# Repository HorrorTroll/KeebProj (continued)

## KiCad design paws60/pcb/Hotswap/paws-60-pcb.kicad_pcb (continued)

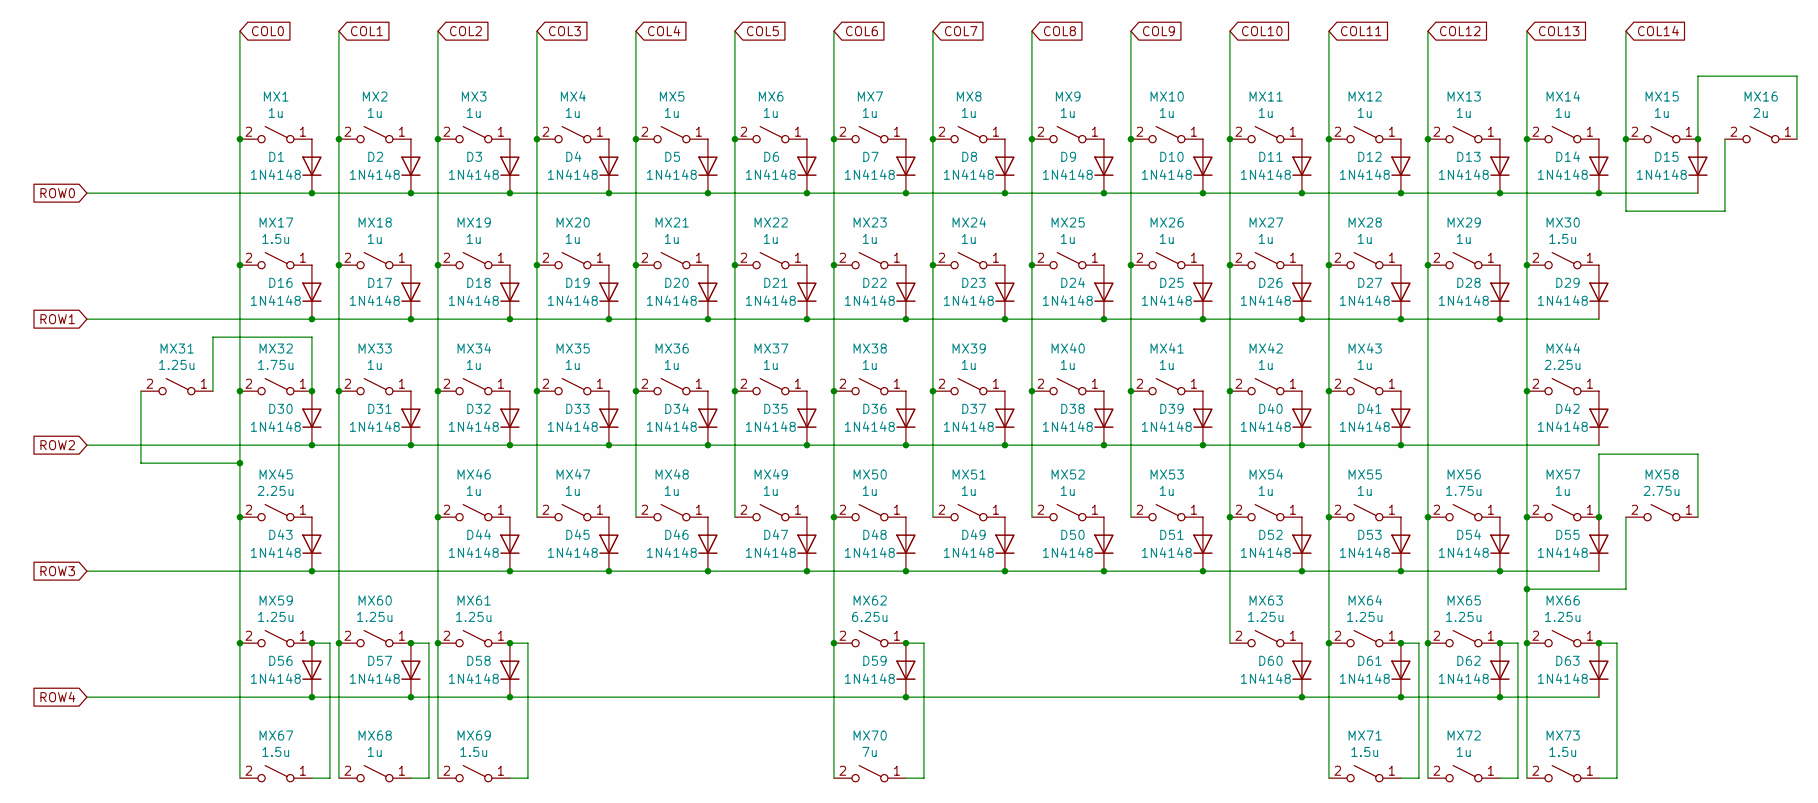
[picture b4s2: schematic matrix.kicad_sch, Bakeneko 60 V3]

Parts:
D1, D2, D3, D4, D5, D6, D7, D8, D9, D10, D11, D12, D13, D14, D15, D16, D17, D18, D19, D20, D21, D22, D23, D24, D25, D26, D27, D28, D29, D30, D31, D32, D33, D34, D35, D36, D37, D38, D39, D40, D41, D42, D43, D44, D45, D46, D47, D48, D49, D50, D51, D52, D53, D54, D55, D56, D57, D58, D59, D60, D61, D62, D63: 1N4148; D_SOD-123; LCSC Part # C81598
MX1, MX2, MX3, MX4, MX5, MX6, MX7, MX8, MX9, MX10, MX11, MX12, MX13, MX14, MX15, MX18, MX19, MX20, MX21, MX22, MX23, MX24, MX25, MX26, MX27, MX28, MX29, MX33, MX34, MX35, MX36, MX37, MX38, MX39, MX40, MX41, MX42, MX43, MX46, MX47, MX48, MX49, MX50, MX51, MX52, MX53, MX54, MX55, MX57, MX68, MX72: 1u; MXOnly-1U-Hotswap
MX16: 2u; MXOnly-2U-Hotswap
MX17, MX30, MX67, MX69, MX71, MX73: 1.5u; MXOnly-1.5U-Hotswap
MX31, MX59, MX60, MX61, MX63, MX64, MX65, MX66: 1.25u; MXOnly-1.25U-Hotswap
MX32, MX56: 1.75u; MXOnly-1.75U-Hotswap
MX44, MX45: 2.25u; MXOnly-2.25U-Hotswap
MX58: 2.75u; MXOnly-2.75U-Hotswap
MX62: 6.25u; MXOnly-6.25U-Hotswap-ReversedStabilizers
MX70: 7u; MXOnly-7U-Hotswap

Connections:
COL0: MX1.2 (B), MX17.2 (B), MX31.2 (B), MX32.2 (B), MX45.2 (B), MX59.2 (B), MX67.2 (B); also elsewhere on the board
COL1: MX2.2 (B), MX18.2 (B), MX33.2 (B), MX60.2 (B), MX68.2 (B); also elsewhere on the board
COL2: MX3.2 (B), MX19.2 (B), MX34.2 (B), MX46.2 (B), MX61.2 (B), MX69.2 (B); also elsewhere on the board
COL3: MX4.2 (B), MX20.2 (B), MX35.2 (B), MX47.2 (B); also elsewhere on the board
COL4: MX5.2 (B), MX21.2 (B), MX36.2 (B), MX48.2 (B); also elsewhere on the board
COL5: MX6.2 (B), MX22.2 (B), MX37.2 (B), MX49.2 (B); also elsewhere on the board
COL6: MX7.2 (B), MX23.2 (B), MX38.2 (B), MX50.2 (B), MX62.2 (B), MX70.2 (B); also elsewhere on the board
COL7: MX8.2 (B), MX24.2 (B), MX39.2 (B), MX51.2 (B); also elsewhere on the board
COL8: MX9.2 (B), MX25.2 (B), MX40.2 (B), MX52.2 (B); also elsewhere on the board
COL9: MX10.2 (B), MX26.2 (B), MX41.2 (B), MX53.2 (B); also elsewhere on the board
COL10: MX11.2 (B), MX27.2 (B), MX42.2 (B), MX54.2 (B), MX63.2 (B); also elsewhere on the board
COL11: MX12.2 (B), MX28.2 (B), MX43.2 (B), MX55.2 (B), MX64.2 (B), MX71.2 (B); also elsewhere on the board
COL12: MX13.2 (B), MX29.2 (B), MX56.2 (B), MX65.2 (B), MX72.2 (B); also elsewhere on the board
COL13: MX14.2 (B), MX30.2 (B), MX44.2 (B), MX57.2 (B), MX58.2 (B), MX66.2 (B), MX73.2 (B); also elsewhere on the board
COL14: MX15.2 (B), MX16.2 (B); also elsewhere on the board
unnamed: D1.2 (A), MX1.1 (A)
unnamed: D2.2 (A), MX2.1 (A)
unnamed: D3.2 (A), MX3.1 (A)
unnamed: D4.2 (A), MX4.1 (A)
unnamed: D5.2 (A), MX5.1 (A)
unnamed: D6.2 (A), MX6.1 (A)
unnamed: D7.2 (A), MX7.1 (A)
unnamed: D8.2 (A), MX8.1 (A)
unnamed: D9.2 (A), MX9.1 (A)
unnamed: D10.2 (A), MX10.1 (A)
unnamed: D11.2 (A), MX11.1 (A)
unnamed: D12.2 (A), MX12.1 (A)
unnamed: D13.2 (A), MX13.1 (A)
unnamed: D14.2 (A), MX14.1 (A)
unnamed: D15.2 (A), MX15.1 (A), MX16.1 (A)
unnamed: D16.2 (A), MX17.1 (A)
unnamed: D17.2 (A), MX18.1 (A)
unnamed: D18.2 (A), MX19.1 (A)
unnamed: D19.2 (A), MX20.1 (A)
unnamed: D20.2 (A), MX21.1 (A)
unnamed: D21.2 (A), MX22.1 (A)
unnamed: D22.2 (A), MX23.1 (A)
unnamed: D23.2 (A), MX24.1 (A)
unnamed: D24.2 (A), MX25.1 (A)
unnamed: D25.2 (A), MX26.1 (A)
unnamed: D26.2 (A), MX27.1 (A)
unnamed: D27.2 (A), MX28.1 (A)
unnamed: D28.2 (A), MX29.1 (A)
unnamed: D29.2 (A), MX30.1 (A)
unnamed: D30.2 (A), MX31.1 (A), MX32.1 (A)
unnamed: D31.2 (A), MX33.1 (A)
unnamed: D32.2 (A), MX34.1 (A)
unnamed: D33.2 (A), MX35.1 (A)
unnamed: D34.2 (A), MX36.1 (A)
unnamed: D35.2 (A), MX37.1 (A)
unnamed: D36.2 (A), MX38.1 (A)
unnamed: D37.2 (A), MX39.1 (A)
unnamed: D38.2 (A), MX40.1 (A)
unnamed: D39.2 (A), MX41.1 (A)
unnamed: D40.2 (A), MX42.1 (A)
unnamed: D41.2 (A), MX43.1 (A)
unnamed: D42.2 (A), MX44.1 (A)
unnamed: D43.2 (A), MX45.1 (A)
unnamed: D44.2 (A), MX46.1 (A)
unnamed: D45.2 (A), MX47.1 (A)
unnamed: D46.2 (A), MX48.1 (A)
unnamed: D47.2 (A), MX49.1 (A)
unnamed: D48.2 (A), MX50.1 (A)
unnamed: D49.2 (A), MX51.1 (A)
unnamed: D50.2 (A), MX52.1 (A)
unnamed: D51.2 (A), MX53.1 (A)
unnamed: D52.2 (A), MX54.1 (A)
unnamed: D53.2 (A), MX55.1 (A)
unnamed: D54.2 (A), MX56.1 (A)
unnamed: D55.2 (A), MX57.1 (A), MX58.1 (A)
unnamed: D56.2 (A), MX59.1 (A), MX67.1 (A)
unnamed: D57.2 (A), MX60.1 (A), MX68.1 (A)
unnamed: D58.2 (A), MX61.1 (A), MX69.1 (A)
unnamed: D59.2 (A), MX62.1 (A), MX70.1 (A)
unnamed: D60.2 (A), MX63.1 (A)
unnamed: D61.2 (A), MX64.1 (A), MX71.1 (A)
unnamed: D62.2 (A), MX65.1 (A), MX72.1 (A)
unnamed: D63.2 (A), MX66.1 (A), MX73.1 (A)
ROW0: D1.1 (K), D2.1 (K), D3.1 (K), D4.1 (K), D5.1 (K), D6.1 (K), D7.1 (K), D8.1 (K), D9.1 (K), D10.1 (K), D11.1 (K), D12.1 (K), D13.1 (K), D14.1 (K), D15.1 (K); also elsewhere on the board
ROW1: D16.1 (K), D17.1 (K), D18.1 (K), D19.1 (K), D20.1 (K), D21.1 (K), D22.1 (K), D23.1 (K), D24.1 (K), D25.1 (K), D26.1 (K), D27.1 (K), D28.1 (K), D29.1 (K); also elsewhere on the board
ROW2: D30.1 (K), D31.1 (K), D32.1 (K), D33.1 (K), D34.1 (K), D35.1 (K), D36.1 (K), D37.1 (K), D38.1 (K), D39.1 (K), D40.1 (K), D41.1 (K), D42.1 (K); also elsewhere on the board
ROW3: D43.1 (K), D44.1 (K), D45.1 (K), D46.1 (K), D47.1 (K), D48.1 (K), D49.1 (K), D50.1 (K), D51.1 (K), D52.1 (K), D53.1 (K), D54.1 (K), D55.1 (K); also elsewhere on the board
ROW4: D56.1 (K), D57.1 (K), D58.1 (K), D59.1 (K), D60.1 (K), D61.1 (K), D62.1 (K), D63.1 (K); also elsewhere on the board

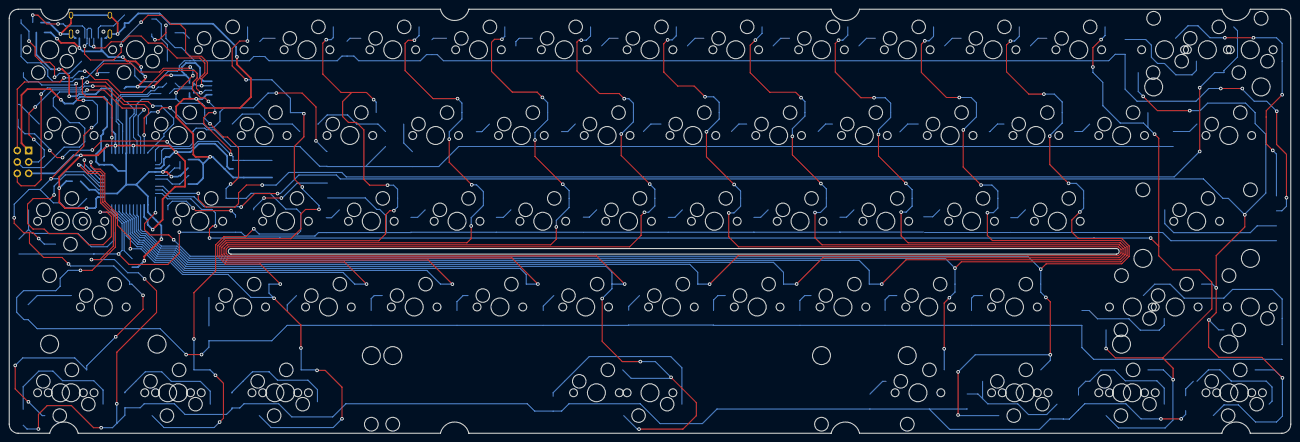
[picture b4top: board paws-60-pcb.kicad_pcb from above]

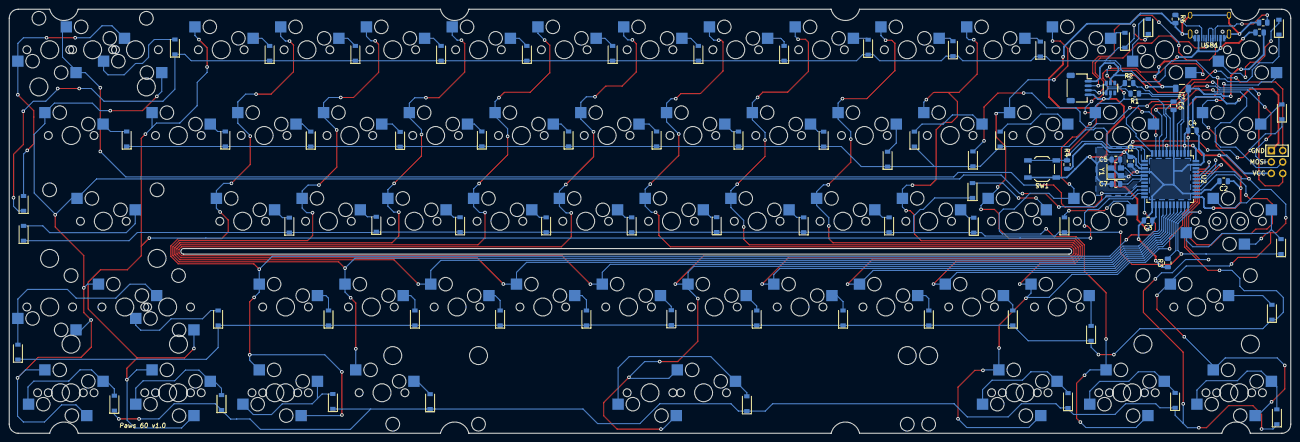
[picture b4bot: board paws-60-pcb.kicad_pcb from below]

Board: 2 copper layers, 284.7 x 94.2 mm, 160 parts (85 on the bottom side), 100 nets.

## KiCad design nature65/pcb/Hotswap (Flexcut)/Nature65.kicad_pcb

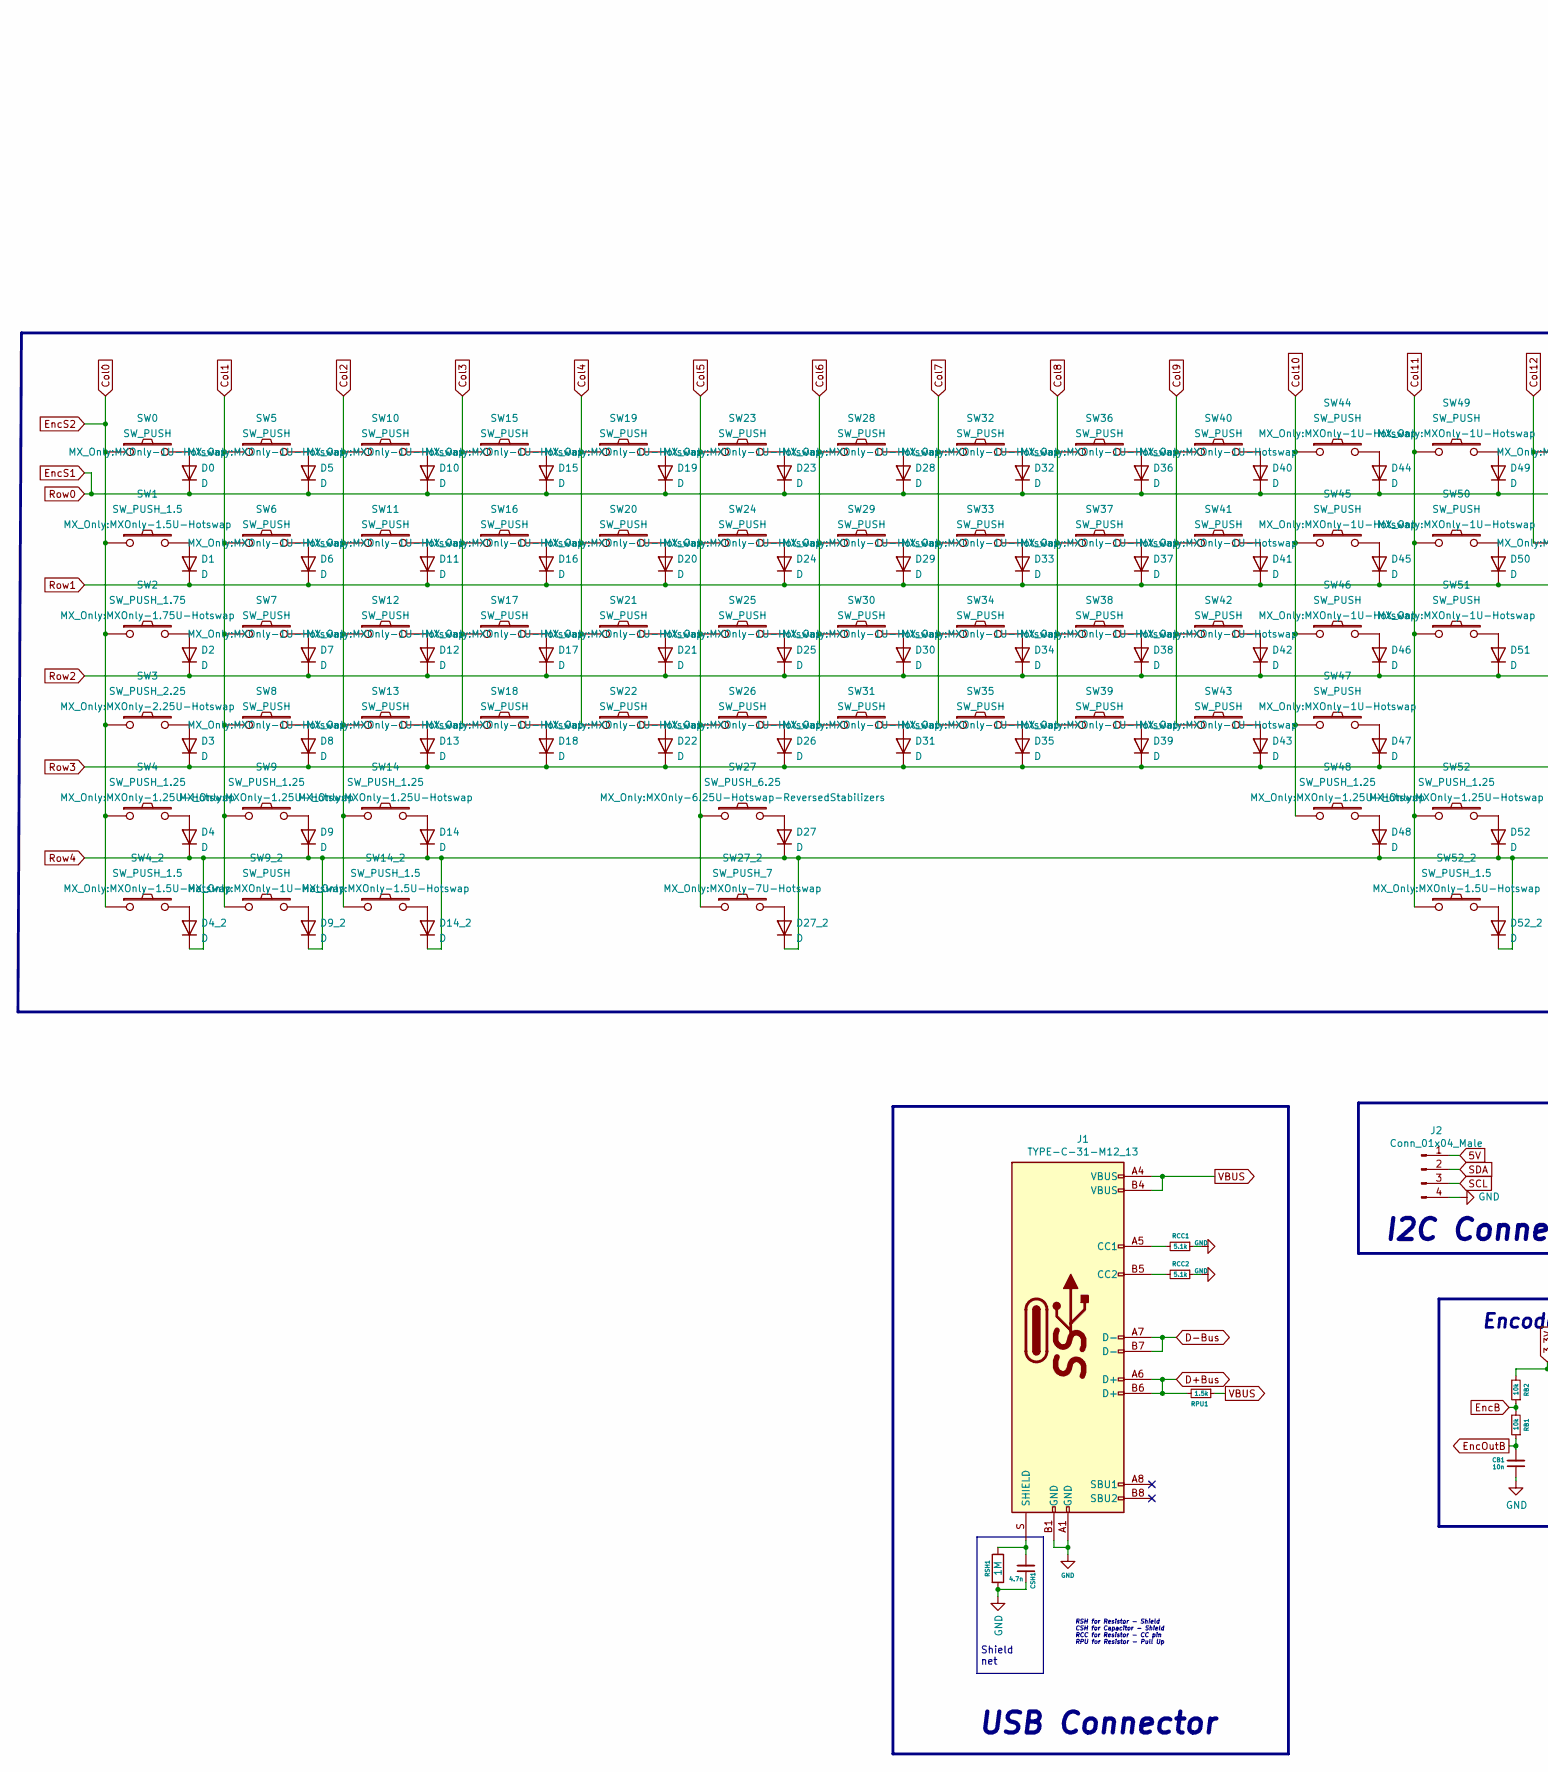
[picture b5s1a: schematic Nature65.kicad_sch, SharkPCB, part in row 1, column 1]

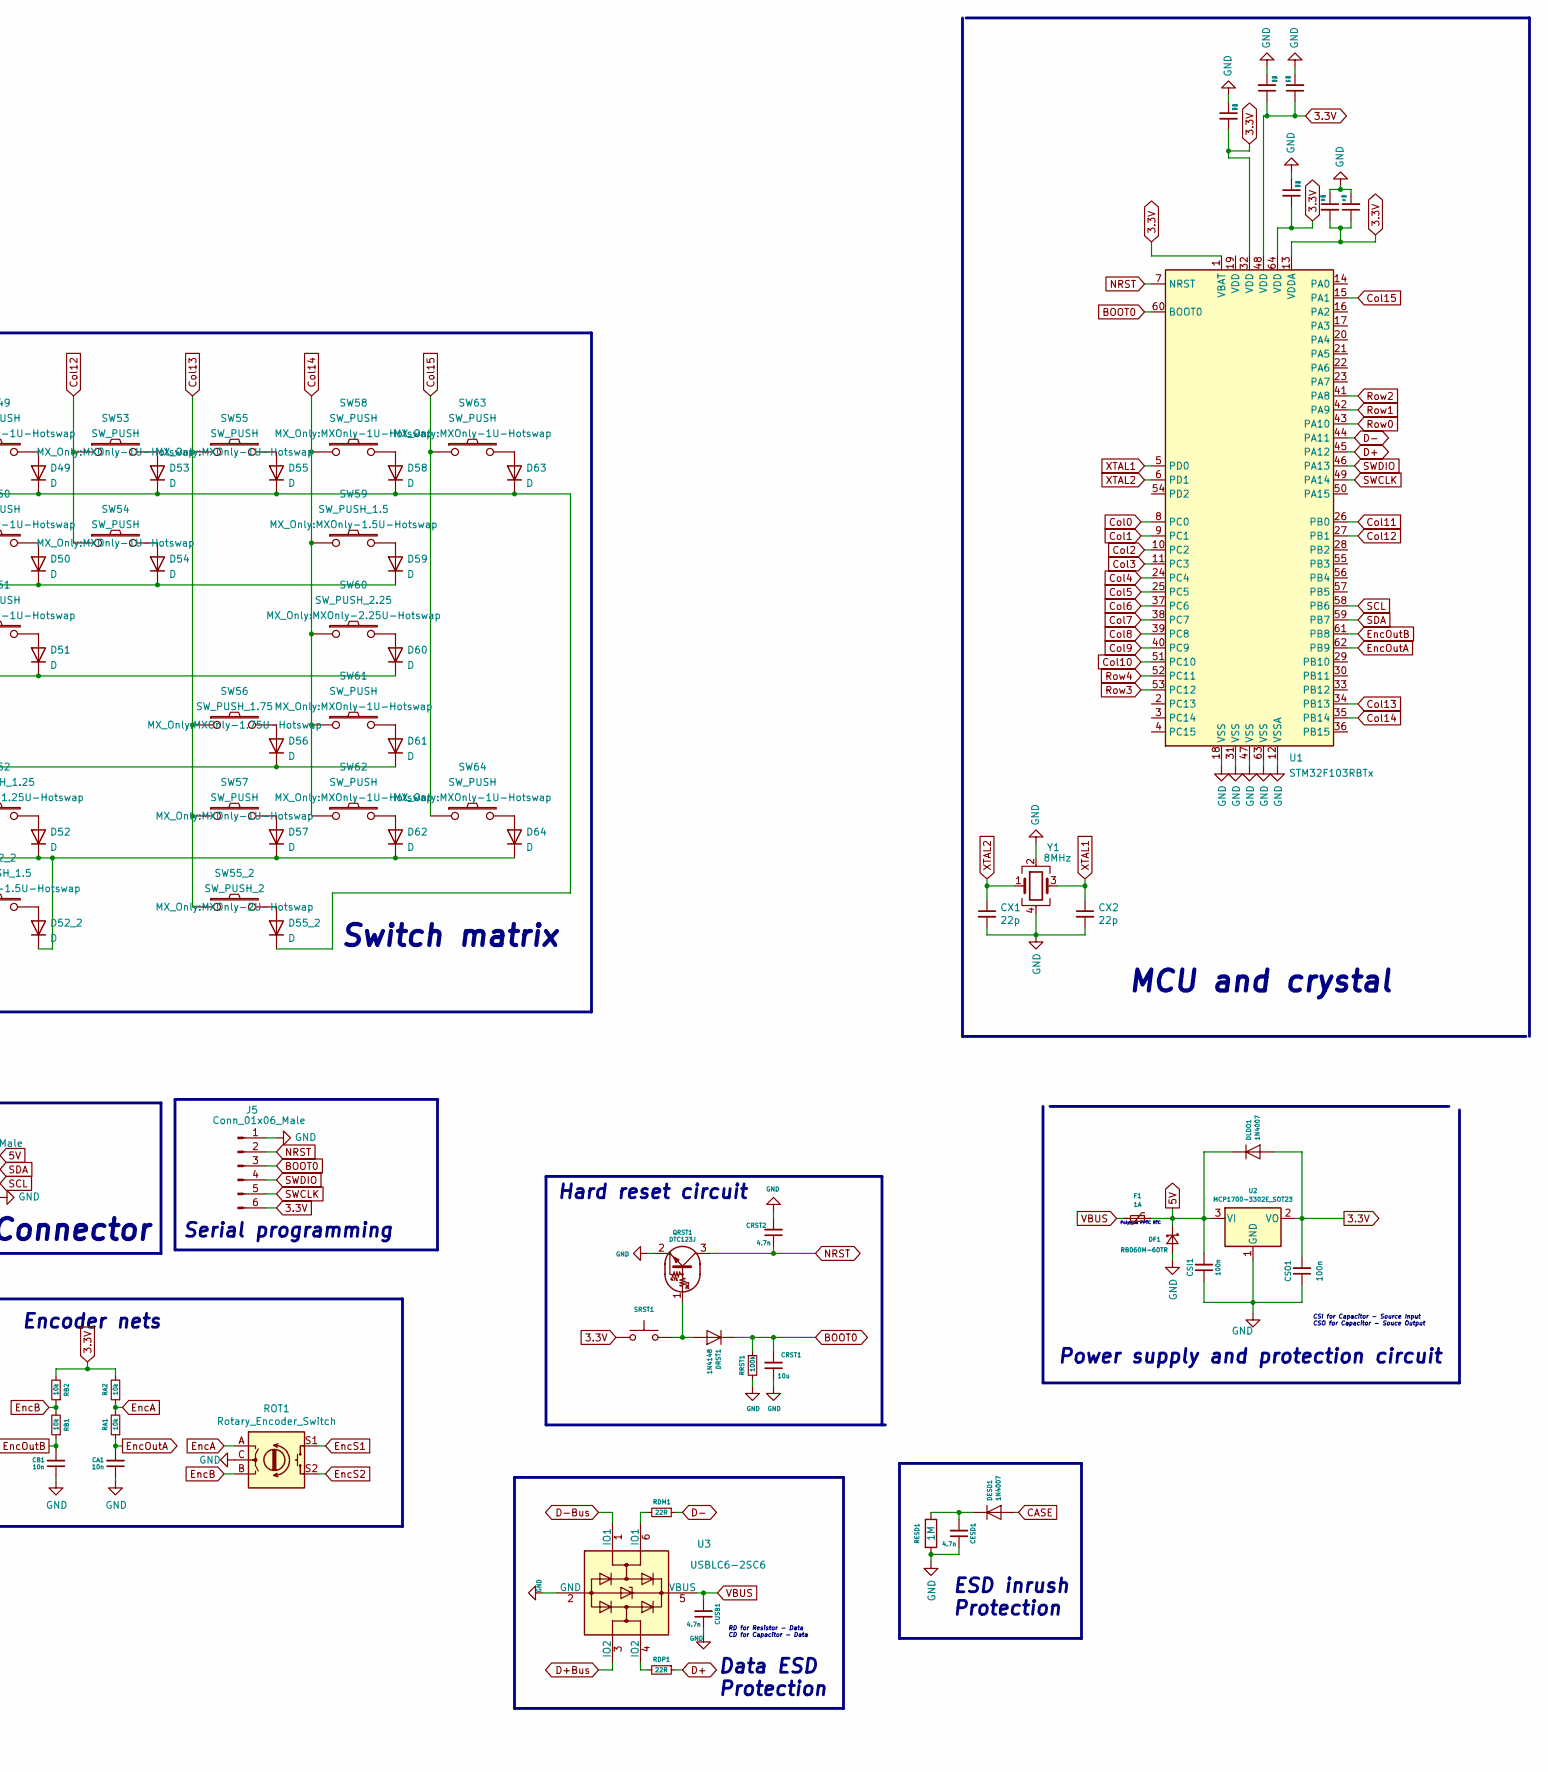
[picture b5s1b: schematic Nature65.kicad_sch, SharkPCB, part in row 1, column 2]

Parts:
CA1: 10n; C_0805_2012Metric_Pad1.18x1.45mm_HandSolder
CB1: 10n; C_0805_2012Metric_Pad1.18x1.45mm_HandSolder
CESD1: 4.7n; C_0805_2012Metric_Pad1.18x1.45mm_HandSolder
CRST1: 10u; C_0805_2012Metric_Pad1.18x1.45mm_HandSolder
CRST2: 4.7n; C_0805_2012Metric_Pad1.18x1.45mm_HandSolder
CSH1: 4.7n; C_0805_2012Metric_Pad1.18x1.45mm_HandSolder
CSI1: 100n; C_0805_2012Metric_Pad1.18x1.45mm_HandSolder
CSO1: 100n; C_0805_2012Metric_Pad1.18x1.45mm_HandSolder
CUSB1: 4.7n; C_0805_2012Metric_Pad1.18x1.45mm_HandSolder
CVB1, CVB2, CVB3: 100n; C_0805_2012Metric_Pad1.18x1.45mm_HandSolder
CVB4: 1u; C_0805_2012Metric_Pad1.18x1.45mm_HandSolder
CVB5: 10n; C_0805_2012Metric_Pad1.18x1.45mm_HandSolder
CVB6: 4.7u; C_0805_2012Metric_Pad1.18x1.45mm_HandSolder
CX1, CX2: 22p; C_0805_2012Metric_Pad1.18x1.45mm_HandSolder
D0, D1, D2, D3, D4, D4_2, D5, D6, D7, D8, D9, D9_2, D10, D11, D12, D13, D14, D14_2, D15, D16, D17, D18, D19, D20, D21, D22, D23, D24, D25, D26, D27, D27_2, D28, D29, D30, D31, D32, D33, D34, D35, D36, D37, D38, D39, D40, D41, D42, D43, D44, D45, D46, D47, D48, D49, D50, D51, D52, D52_2, D53, D54, D55, D55_2, D56, D57, D58, D59, D60, D61, D62, D63, D64: D; D3_SMD_v2
DESD1: 1N4007; D_SOD-123
DF1: RB060M-60TR; D_SOD-123
DLDO1: 1N4007; D_SOD-123
DRST1: 1N4148; D_SOD-123
F1: 1A; Fuse_0805_2012Metric_Pad1.15x1.40mm_HandSolder
J1: TYPE-C-31-M12_13; TYPE-C-31-M-12
J2: Conn_01x04_Male; PinHeader_1x4_P2.54mm_Vertical
J5: Conn_01x06_Male; PinHeader_1x6_P2.54mm_Vertical
QRST1: DTC123J; SOT-23
RA1, RA2: 10k; R_SMD_1206
RB1, RB2: 10k; R_SMD_1206
RCC1, RCC2: 5.1k; R_SMD_1206
RDM1: 22R; R_SMD_1206
RDP1: 22R; R_SMD_1206
RESD1: 1M; R_SMD_1206
ROT1: Rotary_Encoder_Switch; RotaryEncoder_EC11
RPU1: 1.5k; R_SMD_1206
RRST1: 100k; R_SMD_1206
RSH1: 1M; R_SMD_1206
SRST1: SW_Push; SW_SPST_TL3342
SW0, SW5, SW6, SW7, SW8, SW9_2, SW10, SW11, SW12, SW13, SW15, SW16, SW17, SW18, SW19, SW20, SW21, SW22, SW23, SW24, SW25, SW26, SW28, SW29, SW30, SW31, SW32, SW33, SW34, SW35, SW36, SW37, SW38, SW39, SW40, SW41, SW42, SW43, SW44, SW45, SW46, SW47, SW49, SW50, SW51, SW53, SW54, SW55, SW57, SW58, SW61, SW62, SW63, SW64: SW_PUSH; MXOnly-1U-Hotswap
SW1, SW4_2, SW14_2, SW52_2, SW59: SW_PUSH_1.5; MXOnly-1.5U-Hotswap
SW2, SW56: SW_PUSH_1.75; MXOnly-1.75U-Hotswap
SW3, SW60: SW_PUSH_2.25; MXOnly-2.25U-Hotswap
SW4, SW9, SW14, SW48, SW52: SW_PUSH_1.25; MXOnly-1.25U-Hotswap
SW27: SW_PUSH_6.25; MXOnly-6.25U-Hotswap-ReversedStabilizers
SW27_2: SW_PUSH_7; MXOnly-7U-Hotswap
SW55_2: SW_PUSH_2; MXOnly-2U-Hotswap
U1: STM32F103RBTx; LQFP-64_10x10mm_P0.5mm
U2: MCP1700-3302E_SOT23; SOT-23
U3: USBLC6-2SC6; SOT-23-6
Y1: 8MHz; Crystal_SMD_5032-4Pin_5.0x3.2mm

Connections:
3.3V: CSO1.2, CVB1.1, CVB2.2, CVB3.2, CVB4.1, CVB5.2, CVB6.1, DLDO1.2 (A), J5.6, RA2.2, RB2.2, SRST1.1, U1.1 (VBAT), U1.13 (VDDA), U1.32 (VDD), U1.48 (VDD), U1.64 (VDD), U2.2 (VO)
5V: CSI1.2, DF1.1 (K), DLDO1.1 (K), F1.1, J2.1, U2.3 (VI)
BOOT0: CRST1.2, DRST1.1 (K), J5.3, RRST1.1, U1.60 (BOOT0)
CASE: DESD1.2 (A)
Col0: ROT1.S2, SW0.1, SW1.1, SW2.1, SW3.1, SW4.1, SW4_2.1, U1.8 (PC0)
Col1: SW5.1, SW6.1, SW7.1, SW8.1, SW9.1, SW9_2.1, U1.9 (PC1)
Col2: SW10.1, SW11.1, SW12.1, SW13.1, SW14.1, SW14_2.1, U1.10 (PC2)
Col3: SW15.1, SW16.1, SW17.1, SW18.1, U1.11 (PC3)
Col4: SW19.1, SW20.1, SW21.1, SW22.1, U1.24 (PC4)
Col5: SW23.1, SW24.1, SW25.1, SW26.1, SW27.1, SW27_2.1, U1.25 (PC5)
Col6: SW28.1, SW29.1, SW30.1, SW31.1, U1.37 (PC6)
Col7: SW32.1, SW33.1, SW34.1, SW35.1, U1.38 (PC7)
Col8: SW36.1, SW37.1, SW38.1, SW39.1, U1.39 (PC8)
Col9: SW40.1, SW41.1, SW42.1, SW43.1, U1.40 (PC9)
Col10: SW44.1, SW45.1, SW46.1, SW47.1, SW48.1, U1.51 (PC10)
Col11: SW49.1, SW50.1, SW51.1, SW52.1, SW52_2.1, U1.26 (PB0)
Col12: SW53.1, SW54.1, U1.27 (PB1)
Col13: SW55.1, SW55_2.1, SW56.1, SW57.1, U1.34 (PB13)
Col14: SW58.1, SW59.1, SW60.1, SW61.1, SW62.1, U1.35 (PB14)
Col15: SW63.1, SW64.1, U1.15 (PA1)
D+: RDP1.1, U1.45 (PA12)
D+Bus: J1.A6 (D+), J1.B6 (D+), RPU1.2, U3.3 (IO2)
D-: RDM1.1, U1.44 (PA11)
D-Bus: J1.A7 (D-), J1.B7 (D-), U3.1 (IO1)
EncA: RA1.2, RA2.1, ROT1.A
EncB: RB1.2, RB2.1, ROT1.B
EncOutA: CA1.2, RA1.1, U1.62 (PB9)
EncOutB: CB1.2, RB1.1, U1.61 (PB8)
EncS1: D0.1 (K), D5.1 (K), D10.1 (K), D15.1 (K), D19.1 (K), D23.1 (K), D28.1 (K), D32.1 (K), D36.1 (K), D40.1 (K), D44.1 (K), D49.1 (K), D53.1 (K), D55.1 (K), D55_2.1 (K), D58.1 (K), D63.1 (K), ROT1.S1, U1.43 (PA10)
GND: CA1.1, CB1.1, CESD1.1, CRST1.1, CRST2.2, CSH1.1, CSI1.1, CSO1.1, CUSB1.1, CVB1.2, CVB2.1, CVB3.1, CVB4.2, CVB5.1, CVB6.2, CX1.2, CX2.2, DF1.2 (A), J1.A1 (GND), J1.B1 (GND), J2.4, J5.1, QRST1.2 (E), RCC1.1, RCC2.1, RESD1.2, ROT1.C, RRST1.2, RSH1.2, U1.12 (VSSA), U1.18 (VSS), U1.31 (VSS), U1.47 (VSS), U1.63 (VSS), U2.1 (GND), U3.2 (GND), Y1.2, Y1.4
NRST: CRST2.1, J5.2, QRST1.3 (C), U1.7 (NRST)
unnamed: CESD1.2, DESD1.1 (K), RESD1.1
unnamed: CSH1.2, J1.S (SHIELD), RSH1.1
unnamed: D0.2 (A), SW0.2
unnamed: D1.2 (A), SW1.2
unnamed: D2.2 (A), SW2.2
unnamed: D3.2 (A), SW3.2
unnamed: D4.2 (A), SW4.2
unnamed: D4_2.2 (A), SW4_2.2
unnamed: D5.2 (A), SW5.2
unnamed: D6.2 (A), SW6.2
unnamed: D7.2 (A), SW7.2
unnamed: D8.2 (A), SW8.2
unnamed: D9.2 (A), SW9.2
unnamed: D9_2.2 (A), SW9_2.2
unnamed: D10.2 (A), SW10.2
unnamed: D11.2 (A), SW11.2
unnamed: D12.2 (A), SW12.2
unnamed: D13.2 (A), SW13.2
unnamed: D14.2 (A), SW14.2
unnamed: D14_2.2 (A), SW14_2.2
unnamed: D15.2 (A), SW15.2
unnamed: D16.2 (A), SW16.2
unnamed: D17.2 (A), SW17.2
unnamed: D18.2 (A), SW18.2
unnamed: D19.2 (A), SW19.2
unnamed: D20.2 (A), SW20.2
unnamed: D21.2 (A), SW21.2
unnamed: D22.2 (A), SW22.2
unnamed: D23.2 (A), SW23.2
unnamed: D24.2 (A), SW24.2
unnamed: D25.2 (A), SW25.2
unnamed: D26.2 (A), SW26.2
unnamed: D27.2 (A), SW27.2
unnamed: D27_2.2 (A), SW27_2.2
unnamed: D28.2 (A), SW28.2
unnamed: D29.2 (A), SW29.2
unnamed: D30.2 (A), SW30.2
unnamed: D31.2 (A), SW31.2
unnamed: D32.2 (A), SW32.2
unnamed: D33.2 (A), SW33.2
unnamed: D34.2 (A), SW34.2
unnamed: D35.2 (A), SW35.2
unnamed: D36.2 (A), SW36.2
unnamed: D37.2 (A), SW37.2
unnamed: D38.2 (A), SW38.2
unnamed: D39.2 (A), SW39.2
unnamed: D40.2 (A), SW40.2
unnamed: D41.2 (A), SW41.2
unnamed: D42.2 (A), SW42.2
unnamed: D43.2 (A), SW43.2
unnamed: D44.2 (A), SW44.2
unnamed: D45.2 (A), SW45.2
unnamed: D46.2 (A), SW46.2
unnamed: D47.2 (A), SW47.2
unnamed: D48.2 (A), SW48.2
unnamed: D49.2 (A), SW49.2
unnamed: D50.2 (A), SW50.2
unnamed: D51.2 (A), SW51.2
unnamed 89: D52.2 (A), SW52.2; also elsewhere on the board
unnamed: D52_2.2 (A), SW52_2.2
unnamed: D53.2 (A), SW53.2
unnamed: D54.2 (A), SW54.2
unnamed: D55.2 (A), SW55.2
unnamed: D55_2.2 (A), SW55_2.2
unnamed: D56.2 (A), SW56.2
unnamed: D57.2 (A), SW57.2
unnamed: D58.2 (A), SW58.2
unnamed: D59.2 (A), SW59.2
unnamed: D60.2 (A), SW60.2
unnamed: D61.2 (A), SW61.2
unnamed: D62.2 (A), SW62.2
unnamed: D63.2 (A), SW63.2
unnamed: D64.2 (A), SW64.2
unnamed: DRST1.2 (A), QRST1.1 (B), SRST1.2
unnamed: J1.A5 (CC1), RCC1.2
unnamed: J1.B5 (CC2), RCC2.2
unnamed: RDM1.2, U3.6 (IO1)
unnamed: RDP1.2, U3.4 (IO2)
Row1: D1.1 (K), D6.1 (K), D11.1 (K), D16.1 (K), D20.1 (K), D24.1 (K), D29.1 (K), D33.1 (K), D37.1 (K), D41.1 (K), D45.1 (K), D50.1 (K), D54.1 (K), D59.1 (K), U1.42 (PA9)
Row2: D2.1 (K), D7.1 (K), D12.1 (K), D17.1 (K), D21.1 (K), D25.1 (K), D30.1 (K), D34.1 (K), D38.1 (K), D42.1 (K), D46.1 (K), D51.1 (K), D60.1 (K), U1.41 (PA8)
Row3: D3.1 (K), D8.1 (K), D13.1 (K), D18.1 (K), D22.1 (K), D26.1 (K), D31.1 (K), D35.1 (K), D39.1 (K), D43.1 (K), D47.1 (K), D56.1 (K), D61.1 (K), U1.53 (PC12); also elsewhere on the board
Row4: D4.1 (K), D4_2.1 (K), D9.1 (K), D9_2.1 (K), D14.1 (K), D14_2.1 (K), D27.1 (K), D27_2.1 (K), D48.1 (K), D52.1 (K), D52_2.1 (K), D57.1 (K), D62.1 (K), D64.1 (K), U1.52 (PC11)
SCL: J2.3, U1.58 (PB6)
SDA: J2.2, U1.59 (PB7)
SWCLK: J5.5, U1.49 (PA14)
SWDIO: J5.4, U1.46 (PA13)
VBUS: CUSB1.2, F1.2, J1.A4 (VBUS), J1.B4 (VBUS), RPU1.1, U3.5 (VBUS)
XTAL1: CX2.1, U1.5 (PD0), Y1.3
XTAL2: CX1.1, U1.6 (PD1), Y1.1

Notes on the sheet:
Encoder nets
CSI for Capacitor - Source Input CSO for Capacitor - Souce Output
Hard reset circuit
Power supply and protection circuit
MCU and crystal
Switch matrix
Data ESD Protection
Shield net
Polyfuse PPTC RTC
USB Connector
I2C Connector
RSH for Resistor - Shield CSH for Capacitor - Shield RCC for Resistor - CC pin RPU for Resistor - Pull Up
RD for Resistor - Data CD for Capacitor - Data
ESD inrush Protection
Serial programming

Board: 2 copper layers, 187 parts (13 on the bottom side), 119 nets, no tracks yet.

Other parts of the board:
D52#2: D; D3_SMD_v2

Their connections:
unnamed 89: D52#2.2 (A); also elsewhere on the board
Row3: D52#2.1 (K); also elsewhere on the board

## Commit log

2021-09-25 First project
2021-09-25 Forgot the folder
2021-10-13 Updated file
2021-10-14 Added stablizer for 2U spacebar
2021-11-27 Add some project
2021-11-29 Updated PCB for Paws60, remove ISO layout
2021-11-29 Added USB-C port, still not sure it correct or not
2021-11-29 Move crystal more closer to MCU, ya yeet
2021-11-30 Re-wire, ...
2021-11-30 Move diode out, since it was accident block JST port
2021-12-01 Change new mount, blah blah...
2021-12-02 Add logo, and remove usb-c.
2021-12-02 Modify wire a bit, and done.
2021-12-03 Finalize
    More wire modify, better now
2021-12-25 Added Sakura50 keeb pcb
2021-12-25 Update changed for paws60
2021-12-25 Updatted sakura50 files
2021-12-26 Update new layout change for sakura50
2021-12-27 Update 3D Model on Sakura50 pcb, nothing else
2021-12-28 Rotate JST for bettery to match with case
2022-03-10 Added new revision for Sakura50 board
2022-03-26 Updated some issue fix
2022-03-27 Added LDO XC6206, and re-wire a bit
2022-04-17 Added rev 2 for Paws60 pcb
2022-04-17 Added rev 2 for Paws60 pcb (again)
2022-04-17 Some stuff
2022-04-22 Missing aligned, bruh
2022-06-21 Added ToxicDog69 keyboard
2022-06-21 New develop keeb65 keyboard (not final name)
2022-07-08 Added LazuliPad
2022-07-09 Updated LazuliPad a bit
2022-07-20 Update paws60 hotswap socket footprint and lazulipad
2022-08-02 Added new Paws60 (Rev 2)
2022-08-06 Added README file for Paws60
2022-08-07 Update Paws60 (Rev 2) PCB
2022-08-20 Unnecessary commit, but save it just in case anything problem.
